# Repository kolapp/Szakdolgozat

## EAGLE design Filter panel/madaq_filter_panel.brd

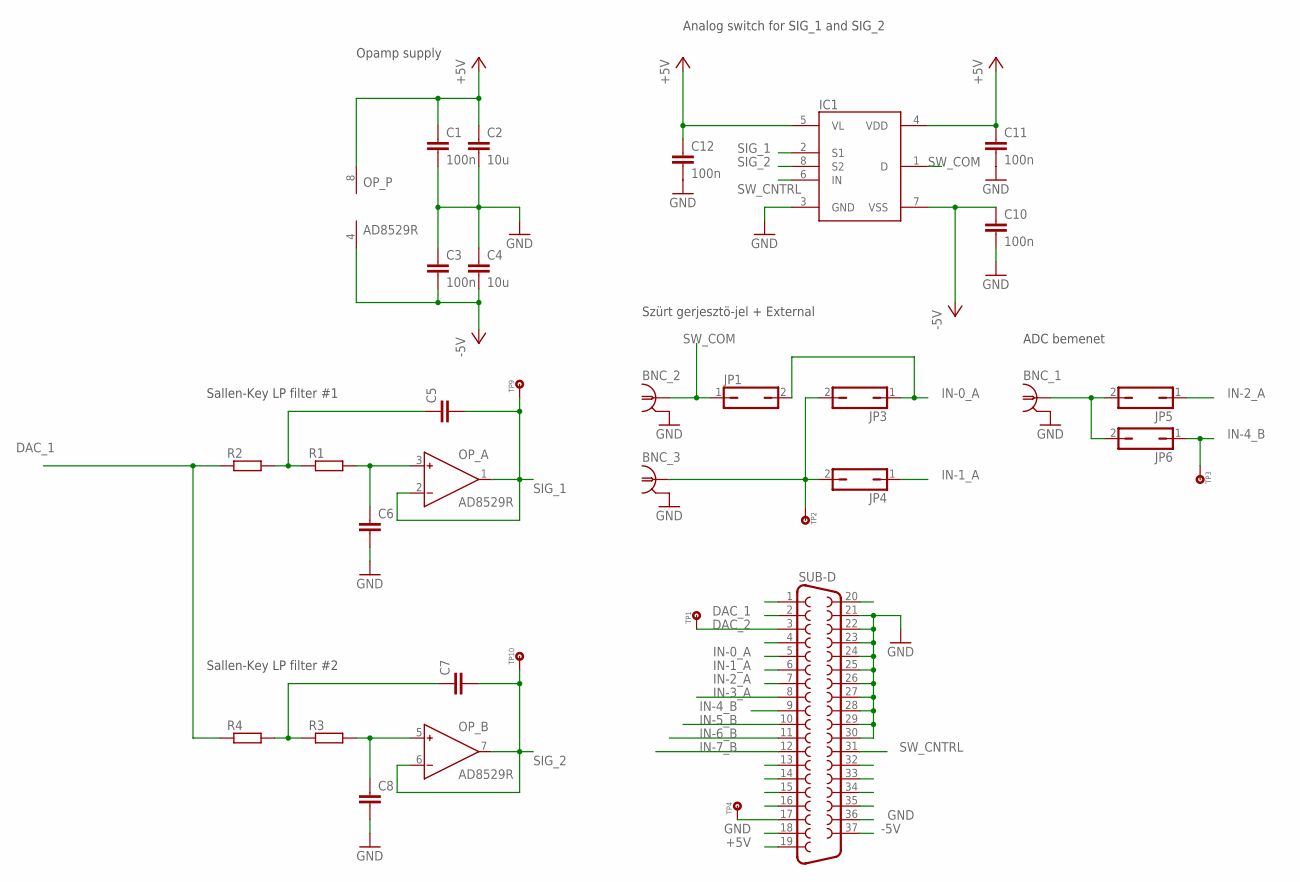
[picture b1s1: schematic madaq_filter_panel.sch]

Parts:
BNC_1, BNC_2, BNC_3: BNC-ISOL-90I; BNCPCB90I
C1, C3, C10, C11, C12: 100n; C1206
C2, C4: 10u; C1206
C5, C6, C7, C8: C1206
IC1: ADG419BR; SO08
JP1, JP3, JP4, JP5, JP6: JP1Q; JP1
OP_: AD8529R; SO8
R1, R2, R3, R4: R1206
SUB-D: F37HP
TP1, TP2, TP3, TP4, TP9, TP10: TP; JP1

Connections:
+5V: C1.2, C2.2, C11.2, C12.2, IC1.4 (VDD), IC1.5 (VL), OP_.8 (V+), SUB-D.19
-5V: C3.1, C4.1, C10.2, IC1.7 (VSS), OP_.4 (V-), SUB-D.37
DAC_1: R2.1, R4.1, SUB-D.2
DAC_2: SUB-D.3, TP1.1
GND: BNC_1.SHIELD, BNC_2.SHIELD, BNC_3.SHIELD, C1.1, C2.1, C3.2, C4.2, C6.1, C8.1, C10.1, C11.1, C12.1, IC1.3 (GND), SUB-D.18, SUB-D.21, SUB-D.22, SUB-D.23, SUB-D.24, SUB-D.25, SUB-D.26, SUB-D.27, SUB-D.28, SUB-D.29, SUB-D.30, SUB-D.36
IN-0_A: JP1.2, JP3.1, SUB-D.5
IN-1_A: JP4.1, SUB-D.6
IN-2_A: JP5.1, SUB-D.7
IN-3_A: SUB-D.8
IN-4_B: JP6.1, SUB-D.9, TP3.1
IN-5_B: SUB-D.10
IN-6_B: SUB-D.11
IN-7_B: SUB-D.12
unnamed: C7.2, R3.1, R4.2
unnamed: C8.2, OP_.5 (IN+), R3.2
unnamed: C5.2, R1.1, R2.2
unnamed: C6.2, OP_.3 (IN+), R1.2
unnamed: BNC_1.SIGNAL, JP5.2, JP6.2
unnamed: BNC_3.SIGNAL, JP3.2, JP4.2, TP2.1
unnamed: SUB-D.17, TP4.1
SIG_1: C5.1, IC1.2 (S1), OP_.1 (OUT), OP_.2 (IN-), TP9.1
SIG_2: C7.1, IC1.8 (S2), OP_.6 (IN-), OP_.7 (OUT), TP10.1
SW_CNTRL: IC1.6 (IN), SUB-D.31
SW_COM: BNC_2.SIGNAL, IC1.1 (D), JP1.1

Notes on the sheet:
Sallen-Key LP filter #1
Sallen-Key LP filter #2
Opamp supply
Analog switch for SIG_1 and SIG_2
Szürt gerjesztö-jel + External
ADC bemenet

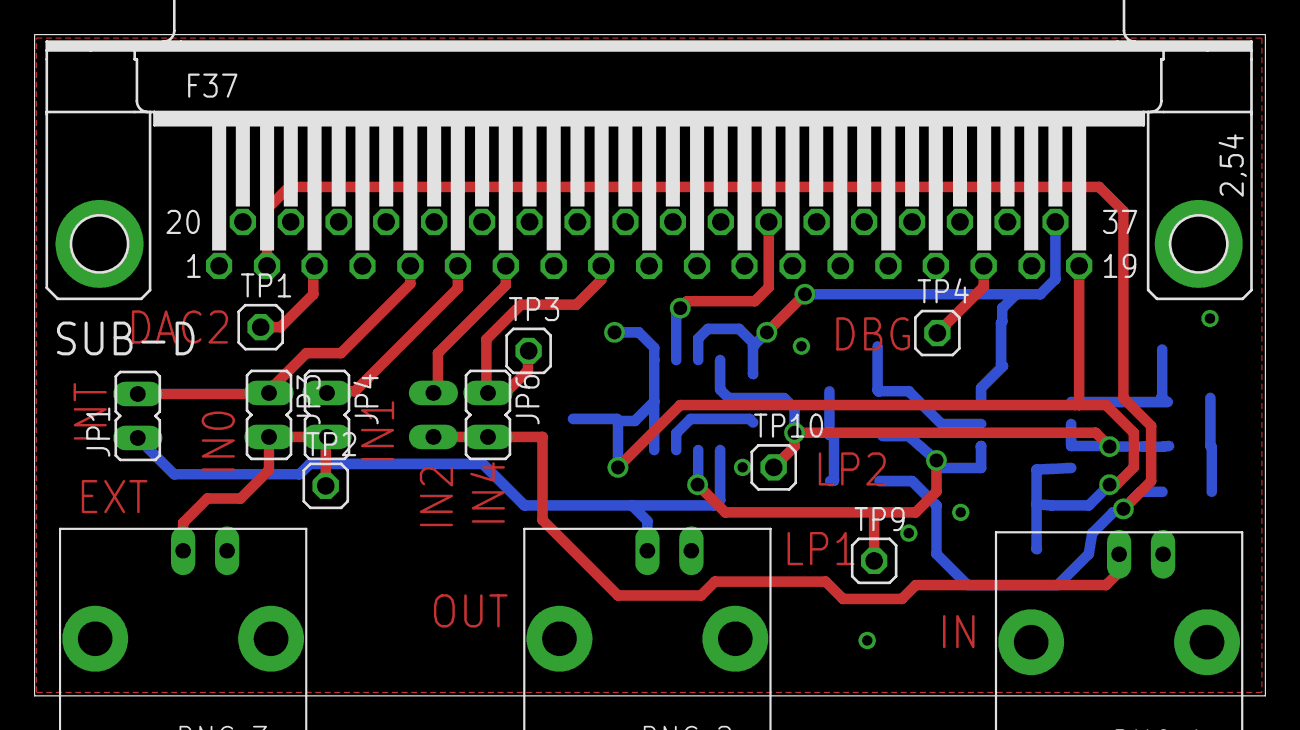
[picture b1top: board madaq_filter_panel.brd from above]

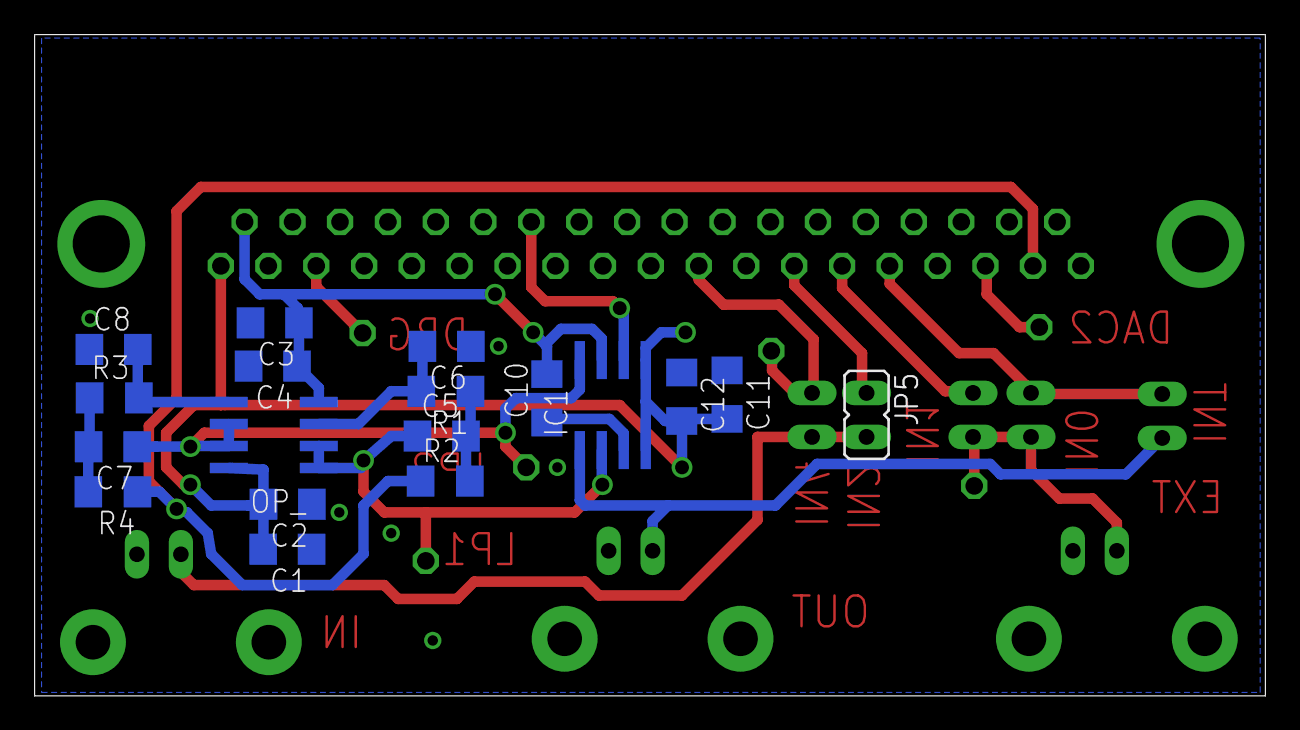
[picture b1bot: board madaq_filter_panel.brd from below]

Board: 2 copper layers, 71.1 x 38.2 mm, 32 parts (18 on the bottom side), 20 nets.

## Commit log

2014-11-03 sync with labor
2014-11-03 - debug makró kókányolás ellen - sar clk control bitekkel játszok: siker = ?
2014-11-05 - config.c és config wizard szinkronba került
2014-11-05 - UART1 kikapcsolva: nem kell - mert adatok gyujtese es kuldese (array)
    - get_samples: mert adatokat fogad es plottol
2014-11-07 - csak kódot igazgattam, várok Robira - nem tudok 129 elem felett generálni :(
2014-11-19 LabView - 2 csatornás mérés (BUGOS: az egyik csatornán mindig egy sinus van??? nem mér rendesen, vagy a tömb rossz)
    Source
    - config: adc1 belőve
    - 2 csatornás mérés féligmeddig implemented
2014-11-25 LabView - felcimkéztem a grafikonokat
    Source
    - most mind2 csatornán egész szépen mér - a furcsa bug eltűnt (???)
2014-11-26 LabView - szebb előlapok, fix méretezés [0; 255]
    Source
    - nemtom
2014-11-27 LabView - TMR2 RLD korlát éheztetés ellen
    Source
    - nem tesztelt / működő __sfr16 hack
    TODO
    - XRAM(i) utasítást használni
    - bájtokat külön kezelni <-- fölösleges 16 bit-es tömbbel dolgozni
2014-12-02 Source - Matattam Jani XRAM-os megoldásával. Talán gyorsabb, de undorítóan átlátható és fos az indexelés is - Működött, de nem működik most. Maderfaker
    Ne revertelj ha lehet. vagy mittomén
2014-12-03 Source - UINT8 elemszam 16 helyett (gyorsabb) - tombkuldes bug javitva
    LabView
    - elemszam kuldes mostmar csak 1 bajtot kuld
2014-12-04 Source - minden méricskélős tömb XRAM-os Jani féle makróval van elérve - @m utasítás 1 period méréséhez - Send_ADC_data() talán jól működik, néha lehet hülyeséget küld - turbó adc interruptok
    LabView
    - @m utasítást használó cucc
2014-12-09 Source - adc0, adc1 priority = high (hátha jobb) - más értelmes változás nincs - teszteltem 5 kHz + 32 mintánál széthal, 16 mintánál szenved a mintavételezéssel
    TODO:
    - 1 interruptban lerendezni a jelgenerálást és mérést is!
2015-01-29 - átmentem egy másik asztalhoz 2 hónap után
2015-01-29 - megint másik asztalhoz megyek
2015-01-29 - cleanin up
2015-02-04 Source - 3 interruptot 1be összenyomtam
2015-02-05 Source - ADC interrrupt full ASM lett + 50% sebesség javulás (über opt)
    Other
    - Kiszámoltam a jelgenerátor korlátait, hány mintát tud max generálni
2015-02-06 Source - Külső kristály osci, belső osci helyett
    LabView
    - SYSCLK = 24 MHz (24.5 helyett)
2015-02-06 cleanup
2015-02-06 LabView - elkezdtem a TF mérést - hülye lebjú összevissza felülírja a cuccait
2015-02-09 LabView - a TF számoló progi már üzemel, de még ronda jelet kapok a madaq-tól (- az első néhány minta hibás)
    Todo
    - visszajelzést küldeni, ha a mérés elkészült (most csak delay-ek várnak az eredményre..)
2015-02-10 Source - adc leáll mérés küldésekor
    LabView
    - mindentudó _Measure 1 Period.vi
    - get_samples.vi hibás volt, javítva lett
    - generate_samples-be raktam egy delayt, mert csakúgy
2015-02-11 Source - minta-indexeles bug javítva - @t tesztelő parancs mérések ellenőrzéséhez scope-on
2015-02-11 LabView - bénaságokat javítottam
2015-02-13 - elkezdtem a szűrős panelt csinálni
2015-02-19 Panel - elkezdtem eagle-ben varázsolni
    - összevontam 2 txt-t
2015-02-20 - konkrét alkatrészlista készül
2015-02-22 Filter panel - panel v1 elkészült (nemtom jó-e) - added Zoli2_2015-02-22 egy TS12A12511 új alkatrésszel
    Tina
    - külön mappába raktam..
2015-02-23 Filter panel - V3 sch + brd
2015-02-24 Filter panel - V4 board (final?)
2015-02-24 Filter panel - V4 sch + brd, Robi és János átnézte - ez nem a megrendelt verzió (János még babrált a board-on)
2015-02-27 Source - kijavítottam az "1. minta hibás bug"-ot
    Labview
    - Measure Transfer Function.vi kegyetlenül HIBÁS volt (dt rosszul kötve+képlet hülyeség)
    - 2 új VI, semmi különös
    - _Sample Generator.vi nem kell
2015-03-03 Labview - Auto scal-eket raktam be, habár idegesítő - 4.5 V input jel
2015-03-04 Labview - úgy tűnik megjavítottam a TF számolós részt, sikerült egy értelmes LP TF-t lemérni - a hülye FLAT TOP szűrő elrontotta a jelemet - adc2volts added, mert hülyeséget számolt 0-65k értékekkel 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
2015-03-05 Labview - kiraktam subVI-ba a TF számolást - átrendeztem a VI-ok lábait
2015-03-06 Labview - csak igazgatás
2015-03-09 Source - DEBUG off
    LabView
    - teszt_sampling_error.vi - mag és phase plot #samples függvényében, fix frekinél
    - Measure 1 Period TF.vi - szépítve
2015-03-11 Source - DAC 0V-ra áll adat küldéskor (idegesítő volt az ugrálás)
    Labview
    - default value-ket beállítottam néhol
    - működő _Measure Transfer Function+optimal.vi
    - calculate_mag_phase.vi: Gaussian ablakozó szűrő hülyeséget csinált, helyette Rect jó
2015-03-11 Filter panel - János upgraded version, R C értékek még kellenek
2015-03-18 Souce - Filter panellel működő kód - P1_3 filter/switch control push pull-ra állítva - kimeneti jel DAC0 helyett DAC1-en megy - @1, @2 adc ch config utasítások
    Labview
    - több periódust is lehet használni
    - optimális izé képletek korrigálva (period <--> samples)
    Filter panel
    - R,C értékek belőve, megépített verzió
2015-03-18 LabView - több periódusos TF számolás bug javítva
2015-03-20 - semmi kül
2015-03-20 Source - @C utasítás szűrő kapcsolgatásához
    LabView
    - generate_samples: freki függő várakozás (fgv)
    Filter panel
    - added 2. board gyártáshoz schematic
2015-03-23 LabView/_Measure Transfer Function+optimal.vi - szűrő állítgatás belőve - periódus bugos volt
2015-03-23 LabView/_Measure Transfer Function+optimal.vi - Config ADC kimaradt, így bugos volt 1. mérésnél - blabllabla
2015-03-24 - most próbálom meg a régi madaq kódhoz integrálni a sajátomat
2015-03-26 MADAQ source/MADAQ20150324 - nem kell, béna
2015-03-26 MADAQ_vanilla - működésbeli változást NINCS! - Computer software is called vanilla when not customized from its original form, meaning that it is used without any customizations or updates applied to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
2015-03-26 - jóvan
2015-03-26 ADC_Config - ADC_Init helyett, kb ugyanazt csinálja - cwg és cfg szinkronban van
2015-03-26 MADAQ_merged - aránylag működő régi madaq AND átviteli fgv mérős kód
2015-03-27 LabView/House heating - elkezdtem
2015-03-30 House heating - aránylag működő sima szimuliáció
2015-03-31 House heating - működik minden, ami eddig kell - még kókány néhol
    MADAQ source
    - Marci kódja
2015-04-03 Source - USB stick-es egyszerű kb működő kód (UART+digital in)
    LabView
    - madaq.llb-s fájlok törölve kívülről
2015-04-03 F410 USB stick - set dac
    LabView/House heating
    - USB stickes működő progik, de még káosz mindenütt
2015-04-07 f410_stick - Changed baud rate to ~1500000 - Changed device info
2015-04-07 House heating - Changed baud rate to 1500000 - Added happiness, outdoor temp - sima függvény hekkelés - SetDAC szépen belőve
2015-04-08 House heating - Changed: STICK_house.vi SZÉP, ZSÍR JÓ MŰKÖDŐ VERZIÓ - Changed: Shit register helyett feedback node a house_model.vi-on BELÜL - Changed: outdoor_temp.vi napi + hosszabb távú hőingás + 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
    - Added brown.vi noise
    - Changed happiness.vi dead zone
2015-04-09 House heating - Fixed: STICK_house.vi Thermostat rosszul volt bekötve - Changed: MADAQ SZÉP ZSÍR house.vi (STICK_house.vi copy paste) - Added: STICK_house_debugOnly.vi kép a portok állapotáról
2015-04-09 House heating - csak átrendeztem, meg 1-2 átnevezés
2015-04-09 LabView - csomó szemét vi törölve - init.vi saját, de device_info.vi, close.vi .llb-ből van
2015-04-10 MADAQ source - Changed: angol kommentek - Added: interrupt disable néhova, mert why not - Removed: 't' cmd - TMR2 enabled, ADC disabled by default
    LabView
    - elvolt írva az adc interrupt ideje!
    - 0.75 duty túl izzasztó, fagyaszt..
    F410 stick source
    - ez meg az
2015-04-14 Added: mese rész
2015-04-16 MADAQ source - kód részeket kidobáltam (deprecated) - commandokat átneveztem hogy ne legyen névütközés
    LabView
    - Added: mag2db.vi
    - Added: send_samples.vi fölösleges-küldés-elkerülő-kódrészlet (néha idióta, de gyors)
2015-04-17 House heating - Changed: get ports now on @p command - Added: @h config command - Changed: néhány vi rossz helyről turkált
    MADAQ source
    - Added: @h config command
2015-04-17 Doksi - elkezdtem írni
2015-04-21 Doksi - csak tartalomjegyzék, szerkezet készül
2015-04-23 House heating - Fixed: kit-en nem lehet negatív feszt mérni - Added: v0 vizsgafeladat for students
2015-04-24 House heating - Be köll szaturálni a feszültségeket - szebb vizsgafeladat
    MADAQ source
    - Initnél 0V dac
2015-04-27 überfosás.
    F410 Stick
    - digital in belőve
    House heating
    - stick-hez új sorrend, lásd vi-ban.
    fakkkjúúúúúúúúúúúúúúúúúúúúúúúúúúúú
2015-04-27 House heating - STICK_house_debugOnly.vi - új ábra - debug only progikhoz villogó led futást indikál - shiny vizsga.docx
    MADAQ source
    - dac 0V startup fix
2015-04-28 House heating - több infó a vizsgában
    F410 Stick
    - fölösleges config kiszedve
    - Vref jobban beállítva
    MADAQ source
    - negatív logika input
2015-04-28 House heating - house.vi szépítgetés - nem kell negatív logika a kit-en
2015-04-28 formazott house heating megoldas...
2015-05-10 - készül.. - TF még nincs
2015-05-11 - Robinak elküldött első rev
2015-05-13 - haladunk szépen.. még 6 oldal - dörög az ég, és késő van
2015-05-15 - konvergálás a 40-hez - Robinak elküldött 2. verzió
2015-05-15 - bocs, semmi
2015-05-16 - bevezetés kész - epic bővítés
2015-05-16 - Robinak elküldött 3. verzió
2015-05-16 - final rev
